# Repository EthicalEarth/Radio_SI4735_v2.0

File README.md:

# Radio_SI4735_v2.0
New version of radio based on chip SI4735.

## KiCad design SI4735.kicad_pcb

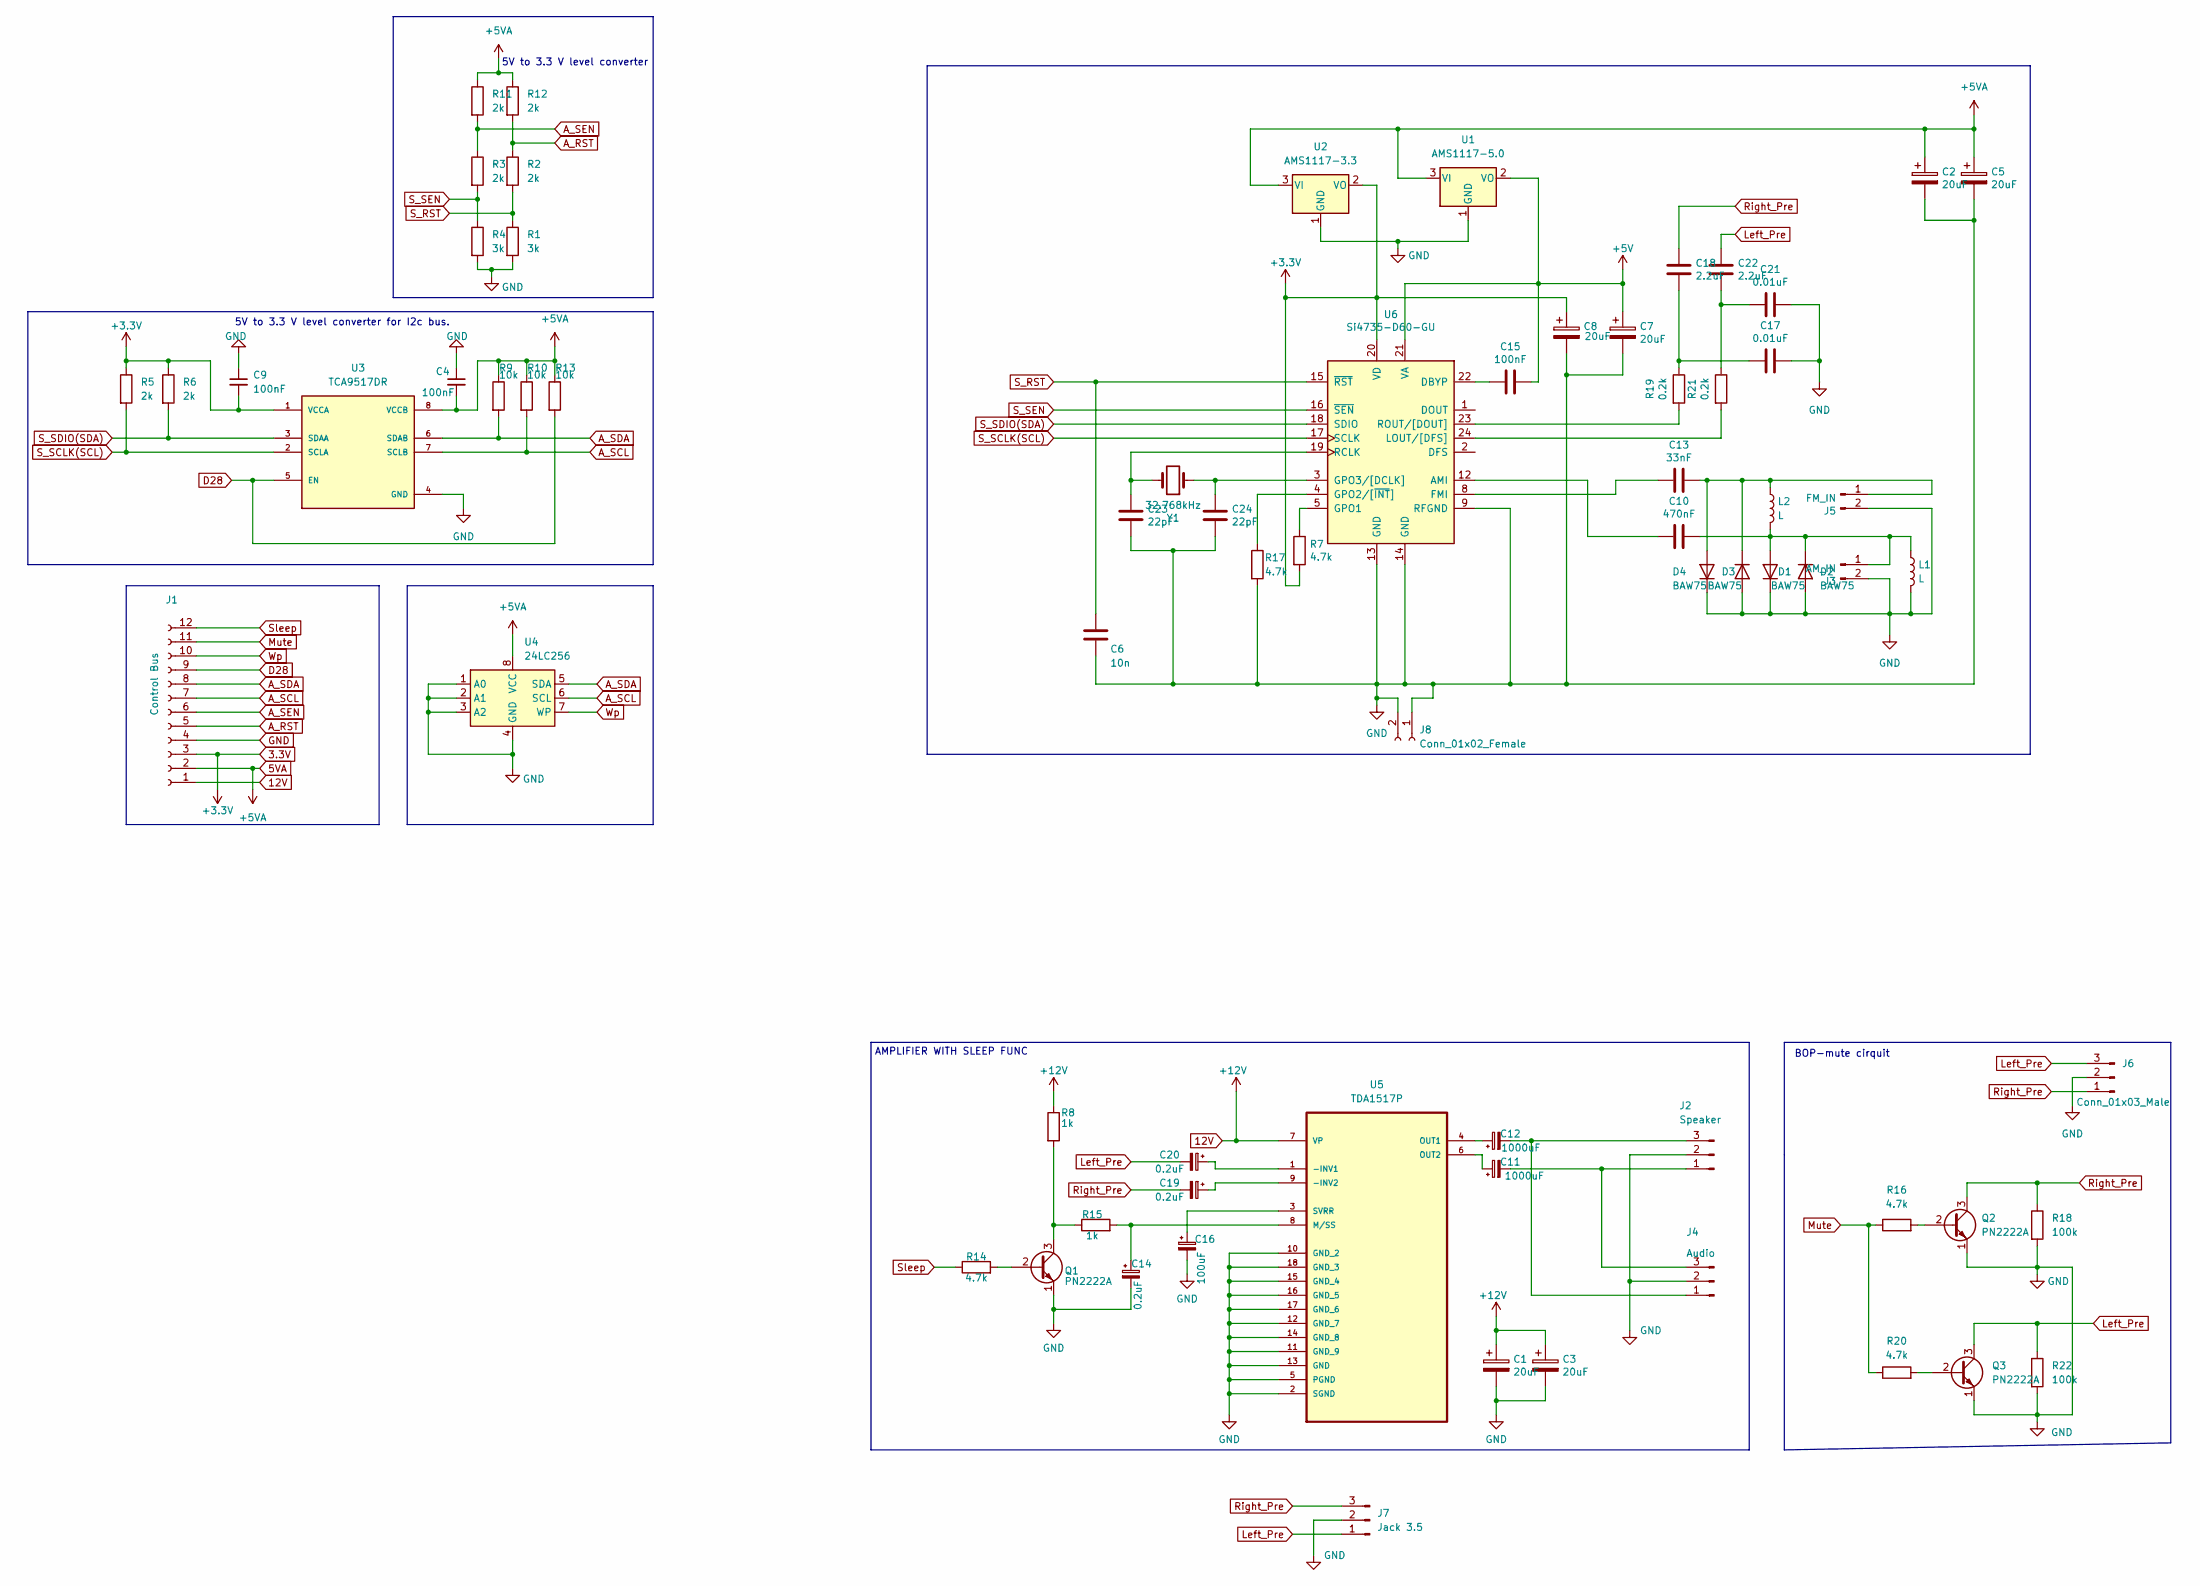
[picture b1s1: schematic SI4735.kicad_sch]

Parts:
C1, C2, C3, C5, C7, C8: 20uF; CP_Radial_D5.0mm_P2.00mm
C4, C9: 100nF; C_1206_3216Metric
C6: 10n; C_1206_3216Metric
C10: 470nF; C_Disc_D4.3mm_W1.9mm_P5.00mm
C11, C12: 1000uF; CP_Radial_D8.0mm_P3.80mm
C13: 33nF; C_Disc_D4.3mm_W1.9mm_P5.00mm
C14, C19, C20: 0.2uF; CP_Radial_D4.0mm_P2.00mm
C15: 100nF; C_Disc_D3.0mm_W1.6mm_P2.50mm
C16: 100uF; CP_Radial_D5.0mm_P2.00mm
C17, C21: 0.01uF; C_Disc_D3.4mm_W2.1mm_P2.50mm
C18, C22: 2.2uF; CP_Radial_D4.0mm_P2.00mm
C23, C24: 22pF; C_1206_3216Metric
D1, D2, D3, D4: BAW75; D_DO-35_SOD27_P7.62mm_Horizontal
J1: Control Bus; PinSocket_1x12_P2.54mm_Vertical
J2: Speaker; PinSocket_1x03_P2.54mm_Vertical
J3: AM_IN; SMA_Amphenol_901-143_Horizontal
J4: Audio; PinSocket_1x03_P2.54mm_Vertical
J5: FM_IN; SMA_Amphenol_901-143_Horizontal
J6: Conn_01x03_Male; PinSocket_1x03_P2.54mm_Vertical
J7: Jack 3.5; PinSocket_1x03_P2.54mm_Vertical
J8: Conn_01x02_Female; JST_NV_B02P-NV_1x02_P5.00mm_Vertical
L1: L; L_Axial_L7.0mm_D3.3mm_P5.08mm_Vertical_Fastron_MICC
L2: L; L_Radial_D6.0mm_P4.00mm
Q1, Q2, Q3: PN2222A; TO-92_Inline_Wide
R1, R4: 3k; R_1206_3216Metric
R2, R3, R5, R6, R11, R12: 2k; R_1206_3216Metric
R7: 4.7k; R_Axial_DIN0309_L9.0mm_D3.2mm_P12.70mm_Horizontal
R8, R15: 1k; R_1206_3216Metric
R9, R10, R13: 10k; R_1206_3216Metric
R14, R16, R17, R20: 4.7k; R_1206_3216Metric
R18, R22: 100k; R_1206_3216Metric
R19, R21: 0.2k; R_1206_3216Metric
U1: AMS1117-5.0; SOT-223-3_TabPin2
U2: AMS1117-3.3; SOT-223-3_TabPin2
U3: TCA9517DR; SOIC127P599X175-8N; PARTREV D
U4: 24LC256; DIP-8_W7.62mm
U5: TDA1517P; DIP254P762X470-18; MPN TDA1517P/N3,112
U6: Si4735-D60-GU; SSOP-24_3.9x8.7mm_P0.635mm
Y1: 32.768kHz; Crystal_C38-LF_D3.0mm_L8.0mm_Horizontal

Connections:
3.3V: C8.1, C9.2, J1.3, R5.1, R6.1, R7.2, U2.2 (VO), U3.1 (VCCA), U6.20 (VD)
5VA: C2.1, C4.2, C5.1, J1.2, R9.1, R10.1, R11.1, R12.1, R13.1, U1.3 (VI), U2.3 (VI), U3.8 (VCCB), U4.8 (VCC)
12V: C1.1, C3.1, J1.1, R8.1, U5.7 (VP)
+5V: C7.1, C15.1, U1.2 (VO), U6.21 (VA)
A_RST: J1.5, R2.1, R12.2
A_SCL: J1.7, R10.2, U3.7 (SCLB), U4.6 (SCL)
A_SDA: J1.8, R9.2, U3.6 (SDAB), U4.5 (SDA)
A_SEN: J1.6, R3.1, R11.2
D28: J1.9, R13.2, U3.5 (EN)
GND: C1.2, C2.2, C3.2, C4.1, C5.2, C6.2, C7.2, C8.2, C9.1, C14.2, C16.2, C17.1, C21.1, C23.2, C24.2, D1.1 (K), D2.2 (A), D3.2 (A), D4.1 (K), J1.4, J2.2, J3.2, J4.2, J5.2, J6.2, J7.2, J8.1, J8.2, L1.2, Q1.1 (E), Q2.1 (E), Q3.1 (E), R1.2, R4.2, R17.2, R18.2, R22.2, U1.1 (GND), U2.1 (GND), U3.4 (GND), U4.1 (A0), U4.2 (A1), U4.3 (A2), U4.4 (GND), U5.2 (SGND), U5.5 (PGND), U5.10 (GND_2), U5.11 (GND_9), U5.12 (GND_7), U5.13 (GND), U5.14 (GND_8), U5.15 (GND_4), U5.16 (GND_5), U5.17 (GND_6), U5.18 (GND_3), U6.9 (RFGND), U6.13 (GND), U6.14 (GND)
Left_Pre: C20.2, C22.1, J6.3, J7.1, Q3.3 (C), R22.1
Mute: J1.11, R16.1, R20.1
unnamed: C17.2, C18.2, R19.1
unnamed: C21.2, C22.2, R21.1
unnamed: C10.1, D1.2 (A), D2.1 (K), J3.1, L1.1, L2.2
unnamed: C13.1, D3.1 (K), D4.2 (A), J5.1, L2.1
unnamed: C11.2, J2.1, J4.3
unnamed: C12.2, J2.3, J4.1
unnamed: Q1.2 (B), R14.2
unnamed: Q1.3 (C), R8.2, R15.1
unnamed: Q2.2 (B), R16.2
unnamed: Q3.2 (B), R20.2
unnamed: C20.1, U5.1 (-INV1)
unnamed: C19.1, U5.9 (-INV2)
unnamed: C14.1, R15.2, U5.8 (M/SS)
unnamed: C12.1, U5.4 (OUT1)
unnamed: C11.1, U5.6 (OUT2)
unnamed: C16.1, U5.3 (SVRR)
unnamed: C10.2, U6.12 (AMI)
unnamed: C15.2, U6.22 (DBYP)
unnamed: C13.2, U6.8 (FMI)
unnamed: R7.1, U6.5 (GPO1)
unnamed: R17.1, U6.4 (GPO2/[~INT])
unnamed: C24.1, U6.3 (GPO3/[DCLK]), Y1.1
unnamed: R21.2, U6.24 (LOUT/[DFS])
unnamed: C23.1, U6.19 (RCLK), Y1.2
unnamed: R19.2, U6.23 (ROUT/[DOUT])
Right_Pre: C18.1, C19.2, J6.1, J7.3, Q2.3 (C), R18.1
S_RST: C6.1, R1.1, R2.2, U6.15 (~RST)
S_SCLK(SCL): R5.2, U3.2 (SCLA), U6.17 (SCLK)
S_SDIO(SDA): R6.2, U3.3 (SDAA), U6.18 (SDIO)
S_SEN: R3.2, R4.1, U6.16 (~SEN)
Sleep: J1.12, R14.1
Wp: J1.10, U4.7 (WP)

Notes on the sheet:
5V to 3.3 V level converter for I2c bus.
5V to 3.3 V level converter
BOP-mute cirquit
AMPLIFIER WITH SLEEP FUNC

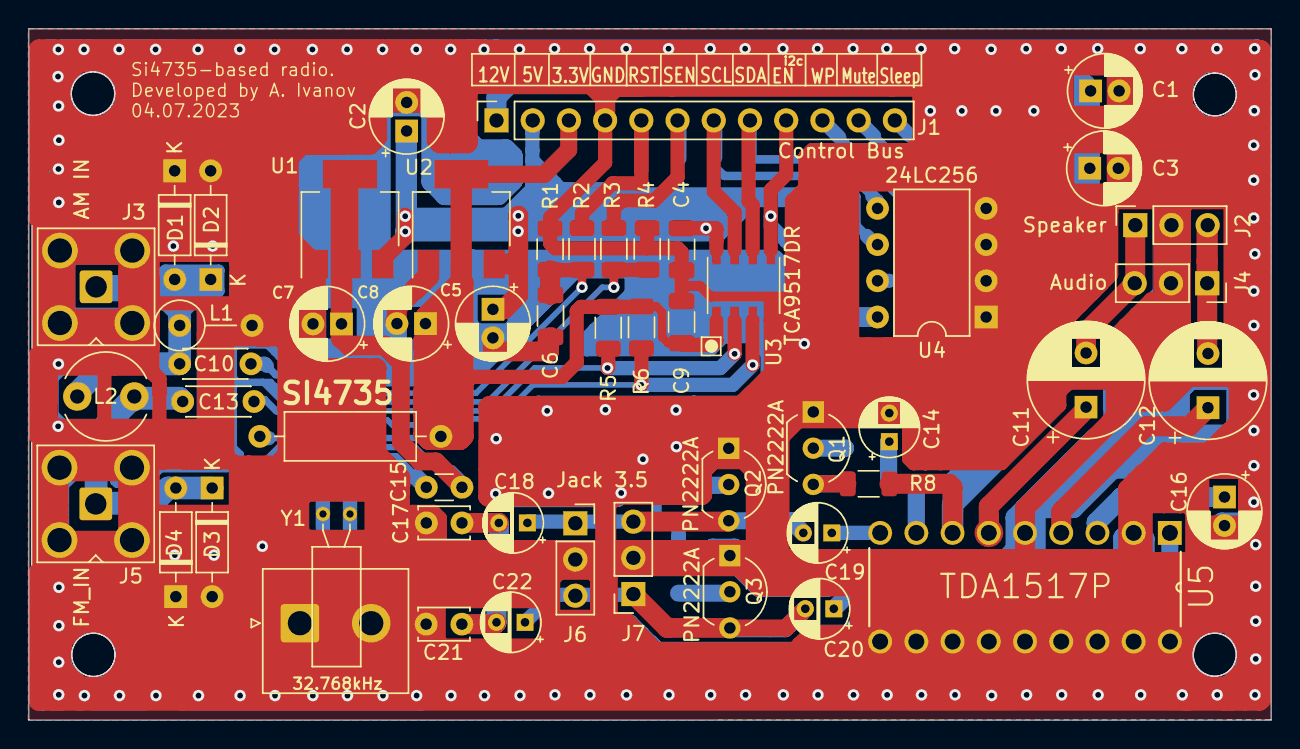
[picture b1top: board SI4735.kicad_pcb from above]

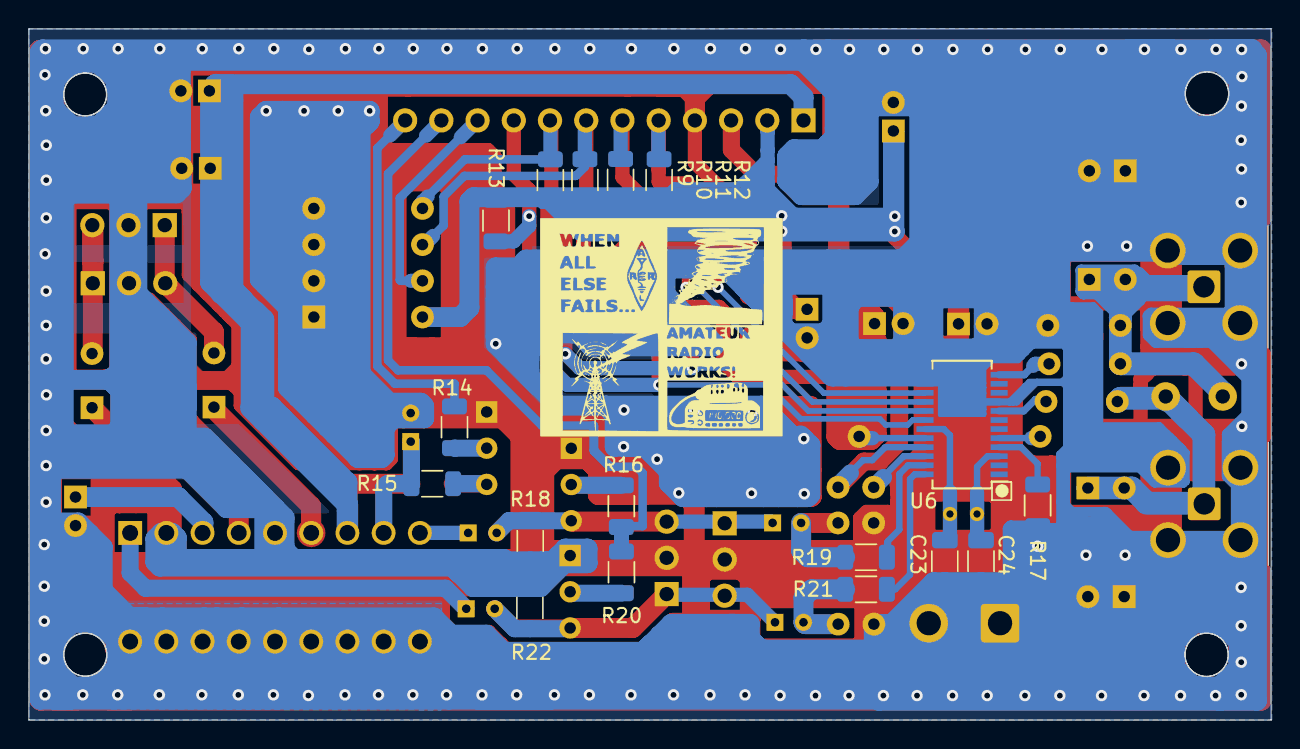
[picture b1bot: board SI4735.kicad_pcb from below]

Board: 2 copper layers, 87.1 x 48.5 mm, 70 parts (17 on the bottom side), 44 nets.

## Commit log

2023-11-05 Initial release.
2023-11-05 Added shared comment to readme
